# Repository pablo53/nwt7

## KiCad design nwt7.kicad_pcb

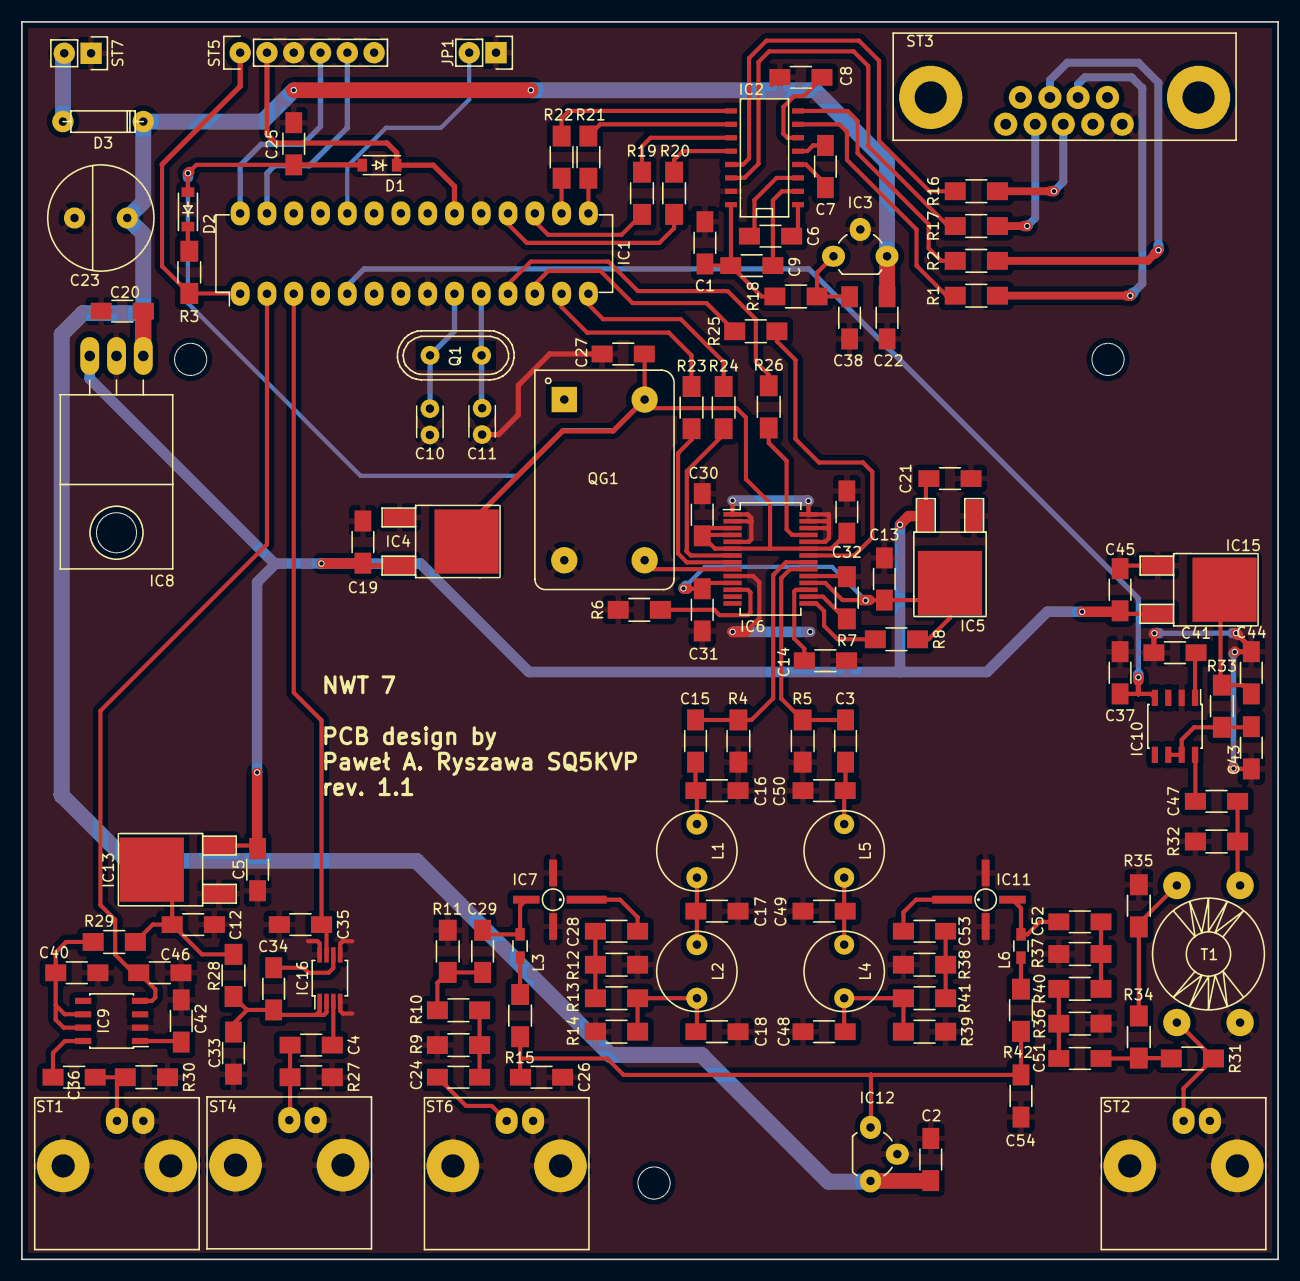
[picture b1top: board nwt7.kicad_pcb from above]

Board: 2 copper layers, 119.1 x 117.3 mm, 130 parts (0 on the bottom side), 93 nets.

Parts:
C1, C2, C6, C7, C8, C9: 1u; C_1206_HandSoldering
C3, C4, C5, C12, C13, C15, C19, C21, C22, C24, C25, C26, C27, C28, C29, C30, C31, C32, C33, C36, C38, C40, C41, C42, C43, C44, C45, C47, C51, C52, C53, C54: 100n; C_1206_HandSoldering
C10, C11: 22p; C_Disc_D3_P2.5
C14, C20: 10u; C_1206_HandSoldering
C16, C17, C18, C48, C49, C50: 60p; C_1206_HandSoldering
C23: 470uF; CE_Radial_D10_L25_P5
C34, C35, C37, C46: 1n; C_1206_HandSoldering
D1, D2: BAT 42; SOD-123
D3: 1N4004; D3
IC1: PIC16F876A; DIP-28_W7.62mm_LongPads
IC2: MAX232; SO-16-N
IC3: 78L05; TO-92_Rugged
IC4, IC5, IC13, IC15: AP1117D50; TO-252-2Lead
IC6: AD9851; SSOP-28_5.3x10.2mm_Pitch0.65mm
IC7, IC11: MSA0886; Micro-X
IC8: 7808; TO-220_Neutral123_Horizontal_LargePads
IC9, IC10: AD8307; SOIC-8_3.9x4.9mm_Pitch1.27mm
IC12: 78L10; TO-92_Rugged
IC16: AD8361; MSOP-8_3x3mm_Pitch0.65mm
JP1: PGM; Pin_Header_Straight_1x02
L1, L2, L4, L5: 180n; INDUCTOR_V
L3, L6: 10u; R_0603_HandSoldering
Q1: 10 MHz; Crystal_HC49-U_Vertical
QG1: 30MHz; KXO-200_LargePads
R1, R2, R12, R14, R16, R17, R38, R39: 100; R_1206_HandSoldering
R3: 10k; R_1206_HandSoldering
R4, R5, R27, R30, R31, R32, R34, R35: 49.9; R_1206_HandSoldering
R6: 3k9; R_1206_HandSoldering
R7, R8, R23, R24, R25, R26: 1k; R_1206_HandSoldering
R9, R11, R36, R37: 300; R_1206_HandSoldering
R10, R40: 18; R_1206_HandSoldering
R13, R15, R41, R42: 68; R_1206_HandSoldering
R18, R19, R20, R21, R22: 20; R_1206_HandSoldering
R28, R29, R33: 10; R_1206_HandSoldering
ST1: IN_LOG; BNC_Socket_Base
ST2: ANT; BNC_Socket_Base
ST3: DB9; DB9_Female_Short
ST4: IN_LIN; BNC_Socket_Base
ST5: PICKIT2; Pin_Header_Straight_1x06
ST6: OUT_DDS; BNC_Socket_Base
ST7: 13.8V; Pin_Header_Straight_1x02
T1: Coupler; Transformer_Amidon-T37

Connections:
GND: C1.2, C2.1, C5.2, C8.1, C10.1, C11.2, C12.1, C13.1, C14.2, C16.2, C17.2, C18.2, C19.1, C20.1, C21.1, C22.2, C23.2, C25.2, C26.2, C27.1, C30.2, C31.2, C32.1, C33.1, C35.2, C37.1, C38.1, C40.2, C41.1, C42.1, C43.2, C44.2, C45.2, C46.1, C48.2, C49.2, C50.2, C54.2, IC1.8, IC1.19, IC2.15, IC3.2, IC4.1, IC5.1, IC6.1, IC6.2, IC6.5, IC6.10, IC6.19, IC6.24, IC6.26, IC6.27, IC6.28, IC7.2, IC7.4, IC8.2, IC9.2, IC10.2, IC11.2, IC11.4, IC12.2, IC13.1, IC15.1, IC16.4, IC16.5, IC16.8, JP1.1, QG1.7, R4.1, R5.2, R6.2, R7.1, R9.2, R11.2, R12.2, R14.2, R27.1, R30.1, R32.1, R35.1, R36.2, R37.2, R38.2, R39.2, ST1.2, ST2.2, ST3.5, ST4.2, ST5.3, ST6.2, ST7.1, T1.1
unnamed: C1.1, C9.2, IC2.16, R18.1
unnamed: C2.2, C20.2, C22.1, C23.1, D3.1, IC3.3, IC8.1, IC12.3
unnamed: C3.1, C50.1, L5.2
unnamed: C3.2, IC6.20, R5.1
unnamed: C4.1, IC16.3
unnamed: C4.2, R27.2, ST4.1
unnamed: C6.1, IC2.1
unnamed: C6.2, IC2.3
unnamed: C7.1, IC2.4
unnamed: C7.2, IC2.5
unnamed: C8.2, IC2.6
unnamed: C9.1, IC2.2
unnamed: C10.2, IC1.9, Q1.2
unnamed: C11.1, IC1.10, Q1.1
unnamed: C12.2, IC13.2, R28.1, R29.2
unnamed: C13.2, C31.1, IC5.2, IC6.11, IC6.18, R8.1
unnamed: C14.1, IC6.17
unnamed: C15.1, IC6.21, R4.2
unnamed: C15.2, C16.1, L1.2
unnamed: C17.1, L1.1, L2.2
unnamed: C18.1, L2.1, R13.2, R14.1
unnamed: C5.1, C19.2, C21.2, C45.1, IC4.3, IC5.3, IC8.3, IC13.3, IC15.3
unnamed: C24.1, R9.1, R10.1
unnamed: C24.2, ST6.1
unnamed: C25.1, C27.2, C30.1, C32.2, D1.2, D2.2, IC4.2, IC6.3, IC6.4, IC6.6, IC6.23, QG1.14
unnamed: C26.1, C54.1, IC12.1, R15.2, R42.1
unnamed: C28.1, IC7.1
unnamed: C28.2, R12.1, R13.1
unnamed: C29.1, IC7.3, L3.2
unnamed: C29.2, R10.2, R11.1
unnamed: C33.2, C34.2, IC16.1, IC16.2, R28.2
unnamed: C34.1, IC16.6
unnamed: C35.1, IC1.3, IC16.7
unnamed: C36.1, R30.2, ST1.1
unnamed: C36.2, IC9.8
unnamed: C37.2, IC1.5, IC10.4
unnamed: C38.2, IC3.1, R18.2
unnamed: C40.1, IC9.6, IC9.7, R29.1
unnamed: C41.2, IC10.1
unnamed: C42.2, IC9.1
unnamed: C43.1, IC10.6, IC10.7, R33.1
unnamed: C44.1, IC15.2, R33.2
unnamed: C46.2, IC1.2, IC9.4
unnamed: C47.1, R32.2, T1.2
unnamed: C47.2, IC10.8
unnamed: C48.1, L4.1, R39.1, R41.2
unnamed: C49.1, L4.2, L5.1
unnamed: C51.1, R36.1, R40.1
unnamed: C51.2, R31.2, R34.2
unnamed: C52.1, IC11.3, L6.1
unnamed: C52.2, R37.1, R40.2
unnamed: C53.1, IC11.1
unnamed: C53.2, R38.1, R41.1
unnamed: D1.1, IC1.20, ST5.2
unnamed: D2.1, R3.1
unnamed: D3.2, ST7.2
unnamed: IC1.1, R3.2, ST5.1
unnamed: IC1.11, R26.2
unnamed: IC1.12, R25.1
unnamed: IC1.13, R23.2
unnamed: IC1.14, R24.1
unnamed: IC1.15, R21.2
unnamed: IC1.16, R22.1
unnamed: IC1.17, R19.2
unnamed: IC1.18, R20.2
unnamed: IC1.24, JP1.2
unnamed: IC1.27, ST5.5
unnamed: IC1.28, ST5.4
unnamed: IC2.7, R1.2
unnamed: IC2.8, R2.1
unnamed: IC2.9, R22.2
unnamed: IC2.10, R21.1
unnamed: IC2.11, R19.1
unnamed: IC2.12, R20.1
unnamed: IC2.13, R16.2
unnamed: IC2.14, R17.1
unnamed: IC6.7, R24.2
unnamed: IC6.8, R23.1
unnamed: IC6.9, QG1.8
unnamed: IC6.12, R6.1
unnamed: IC6.15, R8.2
unnamed: IC6.16, R7.2
unnamed: IC6.22, R25.2
unnamed: IC6.25, R26.1
unnamed: L3.1, R15.1
unnamed: L6.2, R42.2
unnamed: R1.1, ST3.8
unnamed: R2.2, ST3.7
unnamed: R16.1, ST3.3
unnamed: R17.2, ST3.2
unnamed: R31.1, ST2.1, T1.3
unnamed: R34.1, R35.2, T1.4

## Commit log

2021-06-19 init repo...
2021-06-19 linear input - finished
2021-06-23 ver. 1.0
2021-06-23 gerber
2021-06-23 edge cuts
2021-06-23 fixed pcb
2021-06-23 fixed gerber
2021-06-23 polishing pcb
2021-06-24 fixed DB9 conector on PCB
2021-06-24 fixed IC6 desc position
2021-06-24 narrowed PCB
2021-06-24 adjusting
2021-06-24 rings around vias
2021-06-24 schematics
2021-06-25 fixed IC3 power
2021-06-25 rev. 1.01, added PGM jumper
